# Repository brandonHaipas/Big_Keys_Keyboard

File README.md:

# Big_Keys_Keyboard
A new version of the Big Keys PCB, with mostly through hole parts in order to make correcting mistakes easier. the i2c-bus branch is a prototype with a i2c bus that can be shared among all the devices connected through 4 pin JST cables.

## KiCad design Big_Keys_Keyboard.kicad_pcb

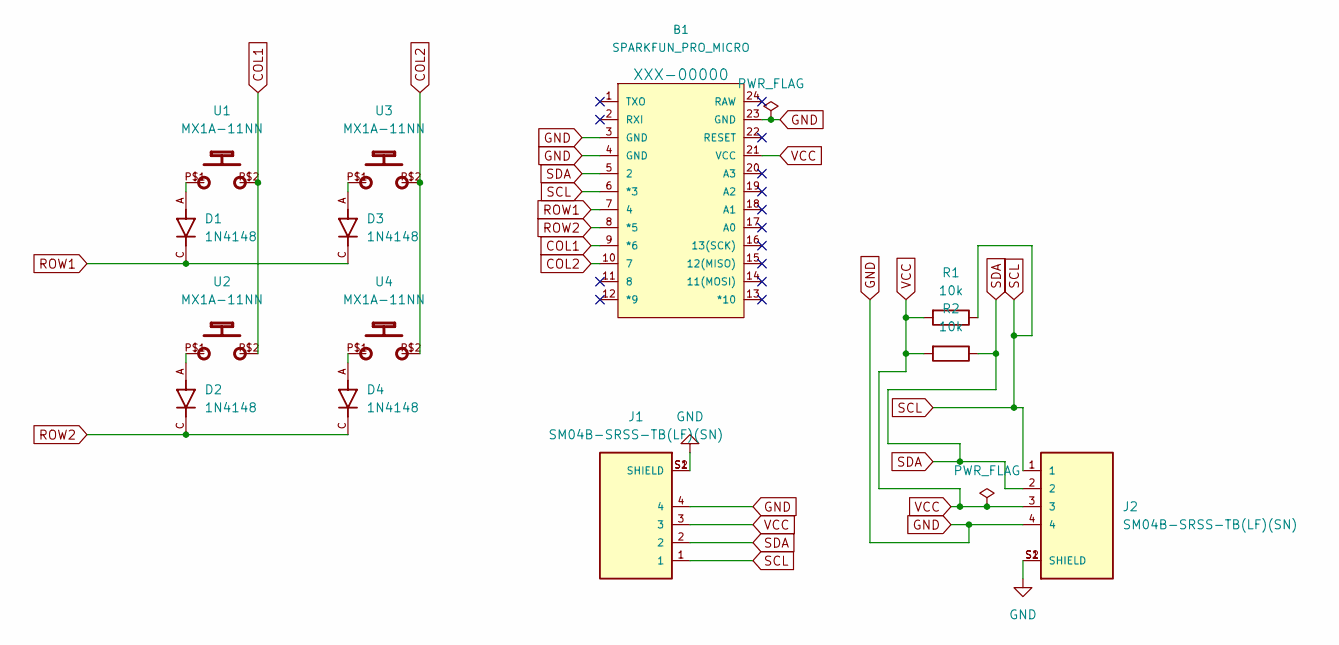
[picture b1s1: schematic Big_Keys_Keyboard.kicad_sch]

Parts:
B1: SPARKFUN_PRO_MICRO
D1, D2, D3, D4: 1N4148; DIOAD829W49L456D191
J1, J2: SM04B-SRSS-TB(LF)(SN); JST_SM04B-SRSS-TB(LF)(SN)
R1, R2: 10k; R_Axial_DIN0207_L6.3mm_D2.5mm_P10.16mm_Horizontal
U1, U2, U3, U4: MX1A-11NN; CHERRY_MX1A-11NN_SWITCH

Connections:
COL1: B1.9 (*6), U1.P$2, U2.P$2
COL2: B1.10 (7), U3.P$2, U4.P$2
GND: B1.3 (GND), B1.4 (GND), B1.23 (GND), J1.4, J1.S1 (SHIELD), J1.S2 (SHIELD), J2.4, J2.S1 (SHIELD), J2.S2 (SHIELD)
unnamed: D1.A, U1.P$1
unnamed: D2.A, U2.P$1
unnamed: D3.A, U3.P$1
unnamed: D4.A, U4.P$1
ROW1: B1.7 (4), D1.C, D3.C
ROW2: B1.8 (*5), D2.C, D4.C
SCL: B1.6 (*3), J1.1, J2.1, R1.1
SDA: B1.5 (2), J1.2, J2.2, R2.1
VCC: B1.21 (VCC), J1.3, J2.3, R1.2, R2.2

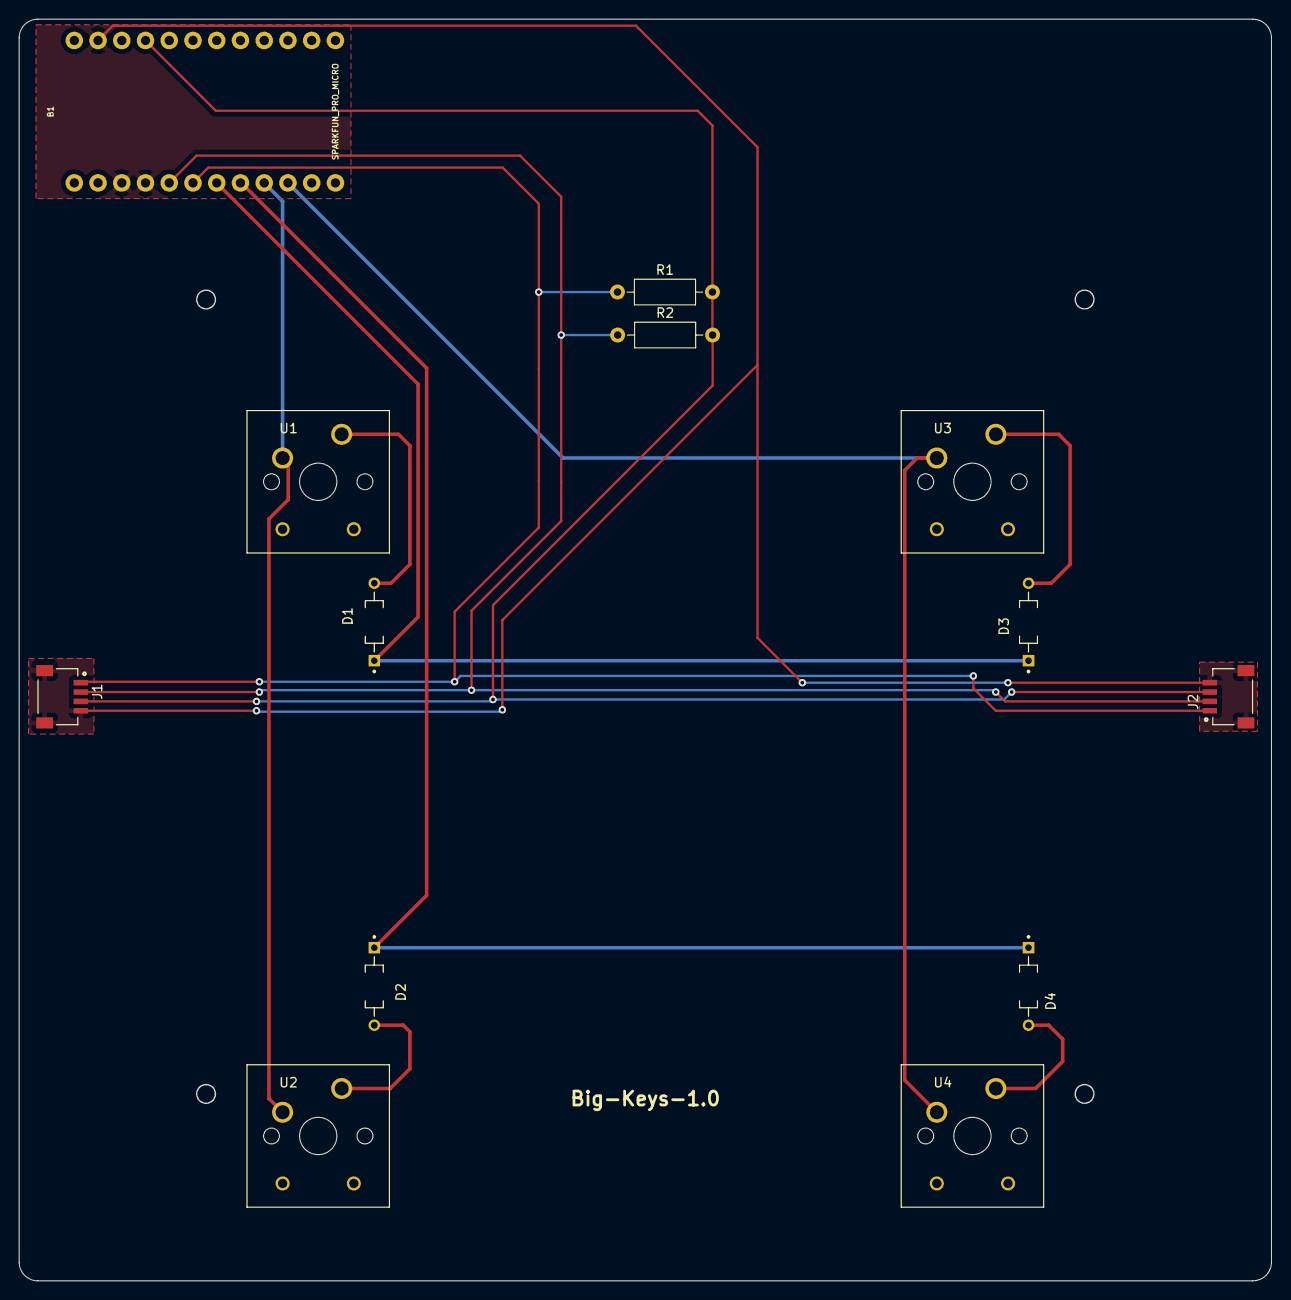
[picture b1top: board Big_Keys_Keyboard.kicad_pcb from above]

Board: 2 copper layers, 134.0 x 135.0 mm, 13 parts (0 on the bottom side), 12 nets.

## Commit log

2023-05-12 schematic done
2023-05-12 components placed in PCB layout
2023-05-15 keyboard routes connected in the PCB
2023-05-16 basic pcb for a 4 keyed board ready
2023-05-19 keyboard with all connections done, lack of i2c
2023-05-23 changed track width to 15 mils
2023-05-23 gerber files for first prototype
2023-05-24 i2c bus with jst 4 pin ports on each side connected
2023-05-25 track width changed to 0.5mm and zones filled with ground net
2023-05-26 surface around i2c ports filled with f. cu connected to GND net
2023-05-26 switch placement hole size changed to fit the drill size
2023-05-26 hole size modified for switch placement holes
2023-05-31 PCB resized to fit the size of the keyboard
2023-05-31 printable design ready
2023-07-24 Create LICENSE
    License for KiCad project
